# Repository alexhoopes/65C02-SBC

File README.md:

# 65C02-SBC

My first PCB design inspired by Ben Eater's 6502 YouTube series

KiCad and Gerber files are added - looking for community support in helping make sure I'm not missing anything

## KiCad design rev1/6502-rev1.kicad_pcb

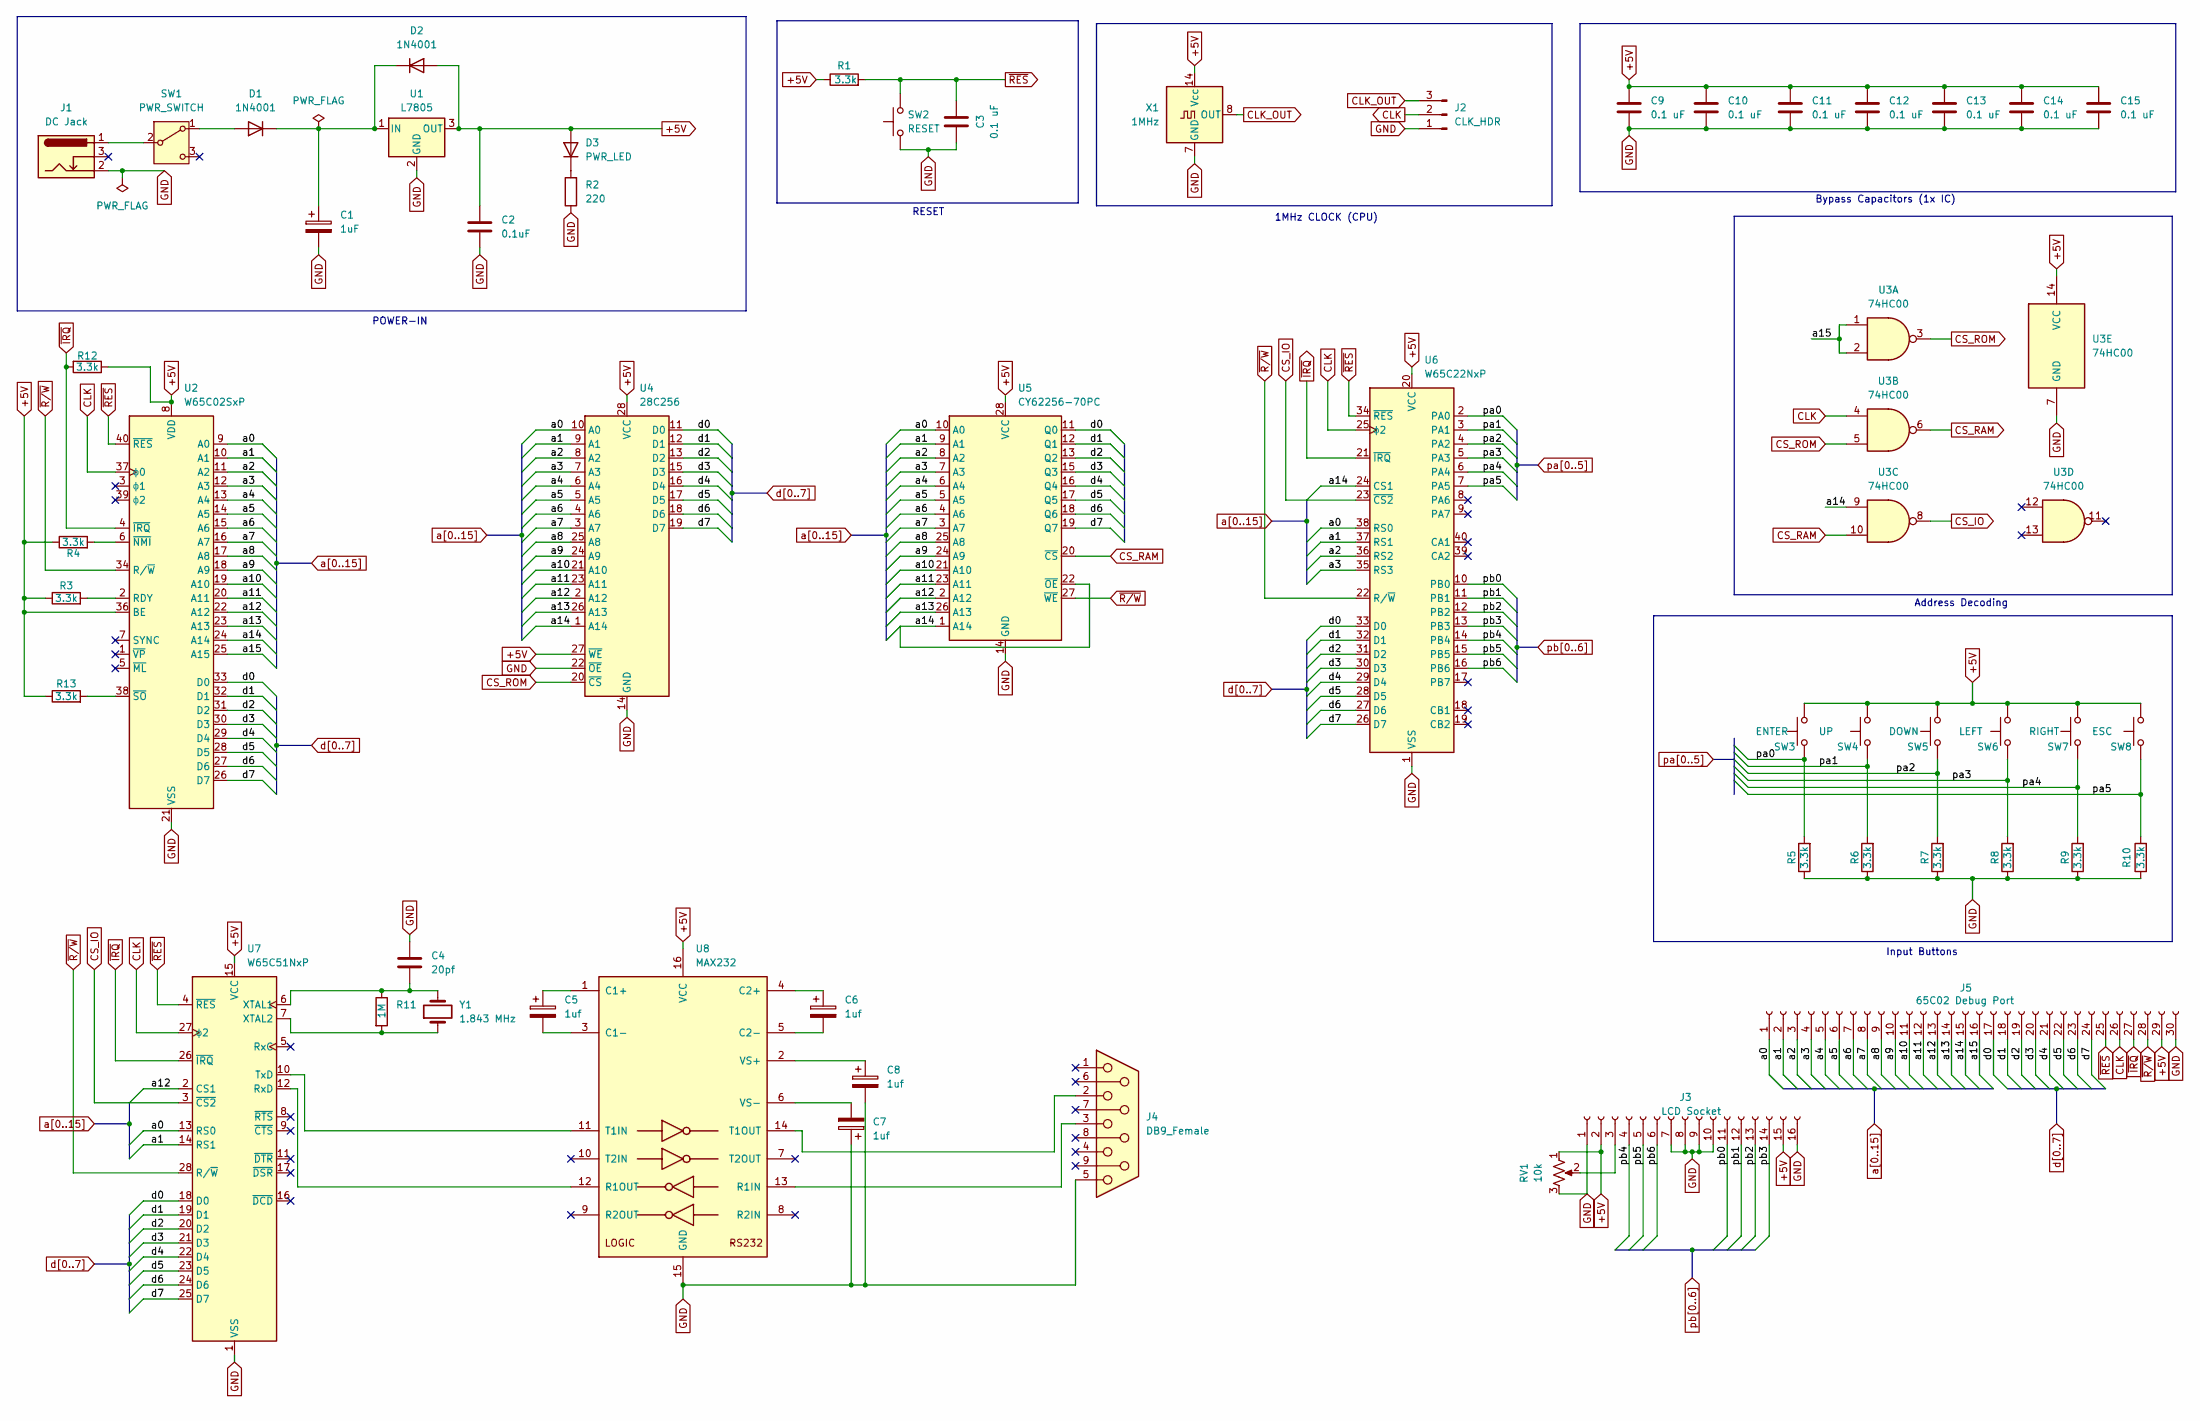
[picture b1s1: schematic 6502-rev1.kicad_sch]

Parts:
C1: 1uF; CAPPRD200W55D500H1220
C2: 0.1uF; C322C104K1R5TA
C3, C9, C10, C11, C12, C13, C14, C15: 0.1 uF; C322C104K1R5TA
C4: 20pf; C322C104K1R5TA
C5, C6, C7, C8: 1uf; CAPPRD200W55D500H1220
D1, D2: 1N4001; DIOAD1530W84L490D260
D3: PWR_LED; 151051BS04000
J1: DC Jack; PJ050AH
J2: CLK_HDR; PinHeader_1x03_P2.54mm_Vertical
J3: LCD Socket; RHDR16W82P0X254_1X16_4114X250X865P
J4: DB9_Female; 09661127600
J5: 65C02 Debug Port; SSW-115-XX-YYY-D
R1, R3, R4, R5, R6, R7, R8, R9, R10, R12, R13: 3.3k; R_Axial_DIN0207_L6.3mm_D2.5mm_P7.62mm_Horizontal
R2: 220; R_Axial_DIN0207_L6.3mm_D2.5mm_P7.62mm_Horizontal
R11: 1M; R_Axial_DIN0204_L3.6mm_D1.6mm_P7.62mm_Horizontal
RV1: 10k; TRIM_PTN06-D10HB20-H
SW1: PWR_SWITCH; SLW12768644AD
SW2: RESET; SW_PUSH_6mm
SW3: ENTER; SW_PUSH_6mm
SW4: UP; SW_PUSH_6mm
SW5: DOWN; SW_PUSH_6mm
SW6: LEFT; SW_PUSH_6mm
SW7: RIGHT; SW_PUSH_6mm
SW8: ESC; SW_PUSH_6mm
U1: L7805; TO255P460X1020X2008-3P
U2: W65C02SxP; DIP-40_W15.24mm_Socket
U3: 74HC00; DIP-14_W7.62mm_Socket
U4: 28C256; 28655410
U5: CY62256-70PC; DIP-28_W15.24mm_Socket
U6: W65C22NxP; DIP-40_W15.24mm_Socket
U7: W65C51NxP; DIP-28_W15.24mm_Socket
U8: MAX232; DIP-16_W7.62mm_Socket
X1: 1MHz; Oscillator_DIP-14
Y1: 1.843 MHz; XTAL_ECS-18-13-1X

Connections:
+5V: C2.1, C9.1, C10.1, C11.1, C12.1, C13.1, C14.1, C15.1, D2.2 (A), D3.2 (A), J3.2, J3.15, J5.29, R1.1, R3.1, R4.1, R12.1, R13.1, RV1.1, SW3.2, SW4.2, SW5.2, SW6.2, SW7.2, SW8.2, U1.3 (OUT), U2.8 (VDD), U2.36 (BE), U3.14 (VCC), U4.27 (~WE), U4.28 (VCC), U5.28 (VCC), U6.20 (VCC), U7.15 (VCC), U8.16 (VCC), X1.14 (Vcc)
CLK: J2.2, J5.26, U2.37 (ϕ0), U3.4, U6.25 (ϕ2), U7.27 (ϕ2)
CLK_OUT: J2.3, X1.8 (OUT)
CS_IO: U3.8, U6.23 (~CS2), U7.3 (~CS2)
CS_RAM: U3.6, U3.10, U5.20 (~CS)
CS_ROM: U3.3, U3.5, U4.20 (~CS)
GND: C1.2, C2.2, C3.1, C4.1, C7.1, C8.2, C9.2, C10.2, C11.2, C12.2, C13.2, C14.2, C15.2, J1.2, J2.1, J3.1, J3.7, J3.8, J3.9, J3.10, J3.16, J4.5, J5.30, R2.1, R5.1, R6.1, R7.1, R8.1, R9.1, R10.1, RV1.3, SW2.1, U1.2 (GND), U2.21 (VSS), U3.7 (GND), U4.14 (GND), U4.22 (~OE), U5.14 (GND), U6.1 (VSS), U7.1 (VSS), U8.15 (GND), X1.7 (GND)
unnamed: D1.2 (A), SW1.1 (A)
unnamed: C1.1, D1.1 (K), D2.1 (K), U1.1 (IN)
unnamed: D3.1 (K), R2.2
unnamed: J3.3, RV1.2
unnamed: J1.1, SW1.2 (B)
unnamed: R3.2, U2.2 (RDY)
unnamed: R4.2, U2.6 (~NMI)
unnamed: R13.2, U2.38 (~SO)
unnamed: U7.12 (RxD), U8.12 (R1OUT)
unnamed: U7.10 (TxD), U8.11 (T1IN)
unnamed: C4.2, R11.1, U7.6 (XTAL1), Y1.2
unnamed: R11.2, U7.7 (XTAL2), Y1.1
unnamed: C5.1, U8.1 (C1+)
unnamed: C5.2, U8.3 (C1-)
unnamed: C6.1, U8.4 (C2+)
unnamed: C6.2, U8.5 (C2-)
unnamed: J4.3, U8.13 (R1IN)
unnamed: J4.2, U8.14 (T1OUT)
unnamed: C8.1, U8.2 (VS+)
unnamed: C7.2, U8.6 (VS-)
a0: J5.1, U2.9 (A0), U4.10 (A0), U5.10 (A0), U6.38 (RS0), U7.13 (RS0)
a1: J5.2, U2.10 (A1), U4.9 (A1), U5.9 (A1), U6.37 (RS1), U7.14 (RS1)
a2: J5.3, U2.11 (A2), U4.8 (A2), U5.8 (A2), U6.36 (RS2)
a3: J5.4, U2.12 (A3), U4.7 (A3), U5.7 (A3), U6.35 (RS3)
a4: J5.5, U2.13 (A4), U4.6 (A4), U5.6 (A4)
a5: J5.6, U2.14 (A5), U4.5 (A5), U5.5 (A5)
a6: J5.7, U2.15 (A6), U4.4 (A6), U5.4 (A6)
a7: J5.8, U2.16 (A7), U4.3 (A7), U5.3 (A7)
a8: J5.9, U2.17 (A8), U4.25 (A8), U5.25 (A8)
a9: J5.10, U2.18 (A9), U4.24 (A9), U5.24 (A9)
a10: J5.11, U2.19 (A10), U4.21 (A10), U5.21 (A10)
a11: J5.12, U2.20 (A11), U4.23 (A11), U5.23 (A11)
a12: J5.13, U2.22 (A12), U4.2 (A12), U5.2 (A12), U7.2 (CS1)
a13: J5.14, U2.23 (A13), U4.26 (A13), U5.26 (A13)
a14: J5.15, U2.24 (A14), U3.9, U4.1 (A14), U5.1 (A14), U5.22 (~OE), U6.24 (CS1)
a15: J5.16, U2.25 (A15), U3.1, U3.2
d0: J5.17, U2.33 (D0), U4.11 (D0), U5.11 (Q0), U6.33 (D0), U7.18 (D0)
d1: J5.18, U2.32 (D1), U4.12 (D1), U5.12 (Q1), U6.32 (D1), U7.19 (D1)
d2: J5.19, U2.31 (D2), U4.13 (D2), U5.13 (Q2), U6.31 (D2), U7.20 (D2)
d3: J5.20, U2.30 (D3), U4.15 (D3), U5.15 (Q3), U6.30 (D3), U7.21 (D3)
d4: J5.21, U2.29 (D4), U4.16 (D4), U5.16 (Q4), U6.29 (D4), U7.22 (D4)
d5: J5.22, U2.28 (D5), U4.17 (D5), U5.17 (Q5), U6.28 (D5), U7.23 (D5)
d6: J5.23, U2.27 (D6), U4.18 (D6), U5.18 (Q6), U6.27 (D6), U7.24 (D6)
d7: J5.24, U2.26 (D7), U4.19 (D7), U5.19 (Q7), U6.26 (D7), U7.25 (D7)
pa0: R5.2, SW3.1, U6.2 (PA0)
pa1: R6.2, SW4.1, U6.3 (PA1)
pa2: R7.2, SW5.1, U6.4 (PA2)
pa3: R8.2, SW6.1, U6.5 (PA3)
pa4: R9.2, SW7.1, U6.6 (PA4)
pa5: R10.2, SW8.1, U6.7 (PA5)
pb0: J3.11, U6.10 (PB0)
pb1: J3.12, U6.11 (PB1)
pb2: J3.13, U6.12 (PB2)
pb3: J3.14, U6.13 (PB3)
pb4: J3.4, U6.14 (PB4)
pb5: J3.5, U6.15 (PB5)
pb6: J3.6, U6.16 (PB6)
~IRQ: J5.27, R12.2, U2.4 (~IRQ), U6.21 (~IRQ), U7.26 (~IRQ)
~RES: C3.2, J5.25, R1.2, SW2.2, U2.40 (~RES), U6.34 (~RES), U7.4 (~RES)
~R/W: J5.28, U2.34 (R/~W), U5.27 (~WE), U6.22 (R/~W), U7.28 (R/~W)

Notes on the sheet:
RESET
Address Decoding
Input Buttons
1MHz CLOCK (CPU)
POWER-IN
Bypass Capacitors (1x IC)

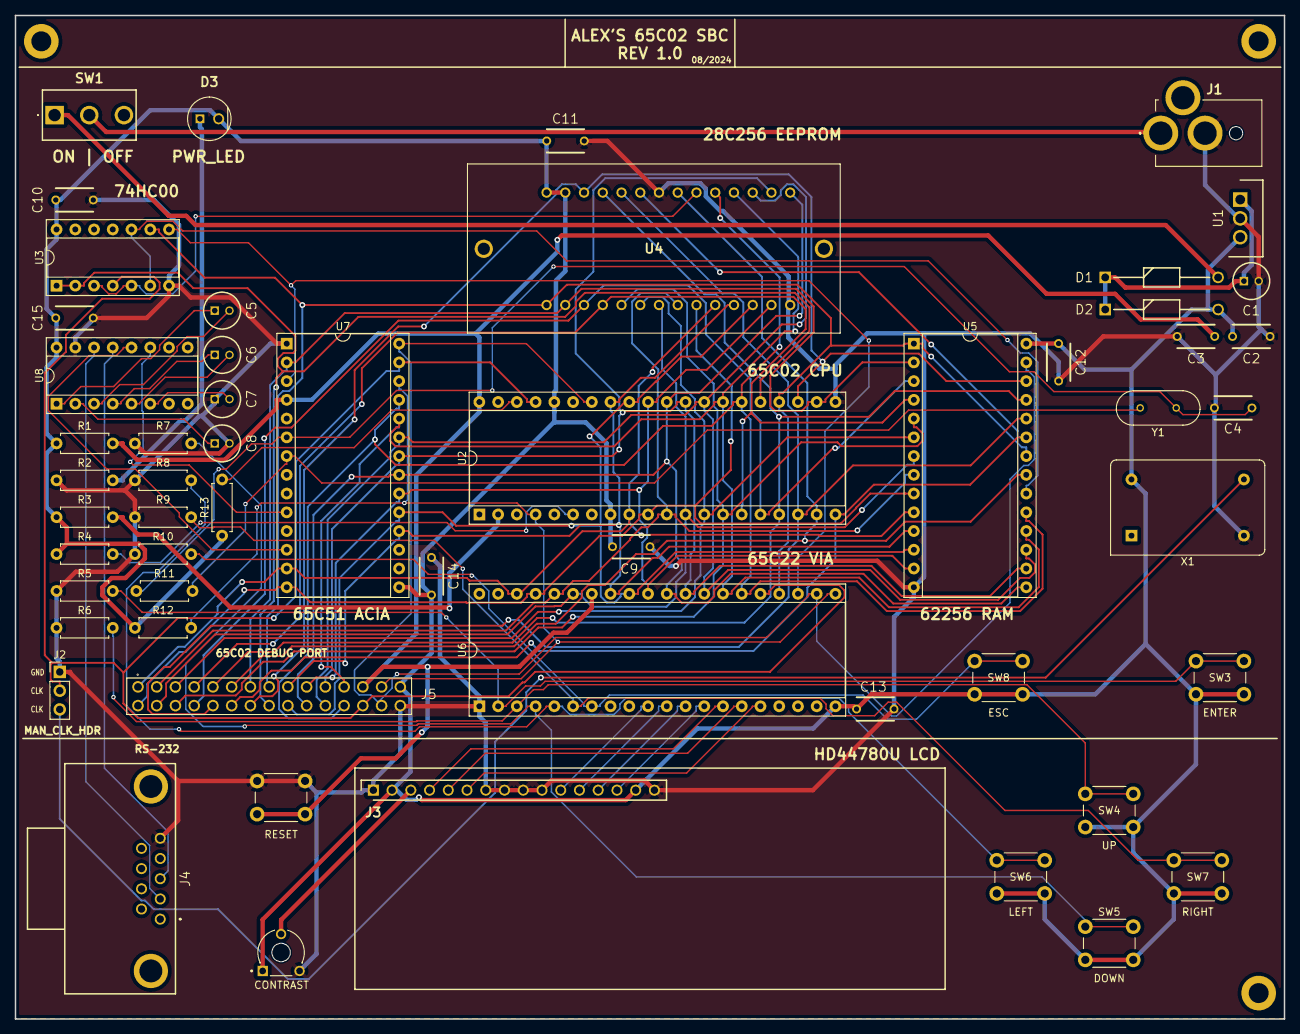
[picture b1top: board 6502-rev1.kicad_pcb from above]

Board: 2 copper layers, 172.0 x 136.0 mm, 58 parts (0 on the bottom side), 67 nets.

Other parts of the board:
MH3, MH4, MH5: MountingHole_2.7mm_M2.5_DIN965_Pad

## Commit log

2024-08-11 Add rev 1 files
